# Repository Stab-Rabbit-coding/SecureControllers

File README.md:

# SecureControllers
unmanned system controllers with security baked in. 

These started as the avionics suite for the Serenity UAV, but aren't limited to that.

1. EMI-Hardened Beagle Capes

    * PocketBeagle2-I Secure Flight Controller
    * PocketBeagle2-I Secure Communications
    * PocketBeagle2-I Sub-Gigahertz Trustworthy Transceiver

2. Trustworthy Sensor R-PI HATs

2. Trustworthy Gateway devices

    * Stackable CAN+RS-485 peripherals Gateway for GPIO/SPI/TTL/ADC/DAC/UART with a TPM.

3. Trustworthy Final Control Elements

    * 50A ESC
    * digital servo
    * Camera/Laser pod
    * Power Distribution Board

## Engineering skills

`skills/` carries four draft Agent Skills for licensed-discipline engineering practice,
pulled from [Griffing-Technology-LLC/engineering-pe-skills](https://github.com/Griffing-Technology-LLC/engineering-pe-skills)
(MIT-licensed; see `skills/ATTRIBUTION.md` and `skills/LICENSE.upstream-MIT`):
`aeronautical-engineering`, `control-systems-engineering`, `mechanical-engineering`,
and `statics-and-dynamics`. **These are still works in progress and are not yet
reviewed or approved by a licensed Professional Engineer in the relevant discipline** —
see each skill's mandatory review notice before relying on any output.

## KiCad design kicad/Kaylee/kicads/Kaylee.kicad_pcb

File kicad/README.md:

# Serenity Avionics — KiCad Cape Status & Build Notes

This directory holds the KiCad projects for the four cape/board types:

| Project | Name | Role |
| --- | --- | --- |
| `Wash.kicad_*` | **Wash** | Flight-control & sensor cape (FC) |
| `TACCO.kicad_*` | **TACCO** | Comms / logging / payload cape (CN) |
| `FlightEngineer.kicad_*` | **FlightEngineer** | Power-distribution board (PDB) |
| `Emma.kicad_*` | **Emma** | 49 MHz (Part 15 §15.235) transceiver |
| `Observer.kicad_*` | **Observer** | Nose/Cargo vision, ToF, & laser board (standalone) |

Per-board net/pin documentation lives in the matching `*.md` files
(`Wash.md`, `TACCO.md`, `FlightEngineer.md`, `XCVR-49MHZ-2.md`). KiCad files keep
KiCad board coordinates (documented exception to the hull-frame standard,
see root `CLAUDE.md`).

---

## DRC / routing work — what was done and what was not (2026-06-12)

A pass was made to wire in a second Ethernet channel and to clear the
Design-Rule-Check (DRC) and ratsnest issues introduced by a manual
component rearrangement. This section records exactly what landed and
what is still open, so the thread can be picked up cleanly.

### ✅ Done

- **Second Ethernet (ETH2) wired on Wash.** The newly placed `ETH2`
  (JST-GH-4P), `ETH2-PHY` (ADIN1300BCPZ), and `T-ETH2` (749010012A
  magnetics) footprints were present but unconnected. Their nets now
  mirror the ETH1 topology exactly:

  ```text
  ETH2 ──ETH2_LINE_{TX,RX}{P,N}──► T-ETH2 ──ETH2_{TX,RX}{P,N}──► ETH2-PHY
  ```

  The host side reuses the nets already broken out on the **PB2-P2**
  header: the `RMII1_*` bus, shared `MDIO`/`MDC`, `PHY2_INTRN`/
  `PHY2_RSTN`, and the `VCC2_ETH` / `GND` / `GND2_ETH` power and
  isolation domains. 44 pads assigned (ETH2-PHY 32, T-ETH2 8, ETH2 4);
  diff-pair chains verified end-to-end. *(Delivered in PR #59.)*

- **Split the two Wash PHYs onto independent MDIO buses (2026-06-12).** Instead
  of an address strap on a shared bus, PHY1 now uses `MDIO0`/`MDC0` (the CPSW
  MDIO controller, PB2-P2 pins 17/18) and PHY2 uses `MDIO1`/`MDC1` (PB2-P2 pins
  1/2, the two spare servo channels SERVO6/7). Each PB2-I NIC manages its own
  PHY — no shared-address conflict. Both the PCB nets and the schematic global
  labels were updated. *Firmware note:* PHY2's bus is a second (bit-banged
  `mdio-gpio`) MDIO; confirm the two repurposed balls are GPIO-capable in the
  PB2-I pinmux.

- **Wired the floating field connectors to their signals (2026-06-12).** Every
  JST field connector was placed but had no nets. Using each footprint's
  Description pinout: SERVO-PWM pads 1–6 → `SERVO0–5` (servo PWM); ESC-TLM →
  `UART_ESC_TX`/`RX`; GPIO-A…F → `GND`/`+3V3` (+ labelled `GPIO_EXP_*` signal);
  CAN-FD → `CAN_H`/`CAN_L`; RS-485 → `RS485_A`/`B`; PWR-IN → `+5V`/`GND`. The
  new connector shorts that DRC now reports are all against `TMESH_*` (the
  pre-existing tamper-mesh overlap, resolved by the mesh rework below) — not the
  connector wiring itself.

- **Confirmed the design is PCB-driven.** Each cape's schematic
  (`*.kicad_sch`) defines only the PocketBeagle-2 header pin-mux (the
  PB2-P1/P2 connectors with the RMII0/RMII1/MDIO net labels); every other
  component lives as a PCB footprint with nets assigned directly on the
  board. "Update PCB from Schematic" therefore does **not** repopulate
  the component nets — net edits are made on the `.kicad_pcb`.

- **Verified the boards load** in `pcbnew` (Wash 43, TACCO 42, Emma 69,
  FlightEngineer 67 footprints) and characterised the violation landscape (below).

### ❌ Not done — open follow-up

1. **Tamper mesh (`TMESH_P`/`TMESH_N`).** Drawn today as a raw
   cross-hatch grid on F.Cu/B.Cu that **shorts across SMD pads and across
   the isolated `GND2_*` domains** — this is the single largest source of
   DRC errors (≈335 of Wash's 465; similar on TACCO). The agreed design is
   a **per-domain anti-tamper mesh**: a separate monitored mesh net per
   isolation region (secure/`GND` area plus one per `GND2_CAN` / `GND2_ETH`
   / `GND2_RS485` field side), with the 0.5 mm `ISOLATION` creepage moat
   kept clear between them. Wash and TACCO tie their mesh to the local TPM;
   **FlightEngineer and Emma have no local TPM**, so their tamper signal must be
   carried over the inter-board link (Emma → TACCO, FlightEngineer → Wash).

2. **Routing / ratsnest.** The manual rearrangement left signal nets
   unrouted (~60 multi-pin signal nets per cape; the 7 power/ground nets
   are intended as planes). This was **not** completed — see the toolchain
   findings below for why headless autorouting did not produce a
   trustworthy result. The impedance-controlled Ethernet pairs should be
   routed interactively (length-matched / controlled-impedance) regardless.

3. **Remaining DRC.** After the mesh and routing are fixed, the residual
   cosmetic/footprint items still need clearing (counts measured
   2026-06-12, error+warning):

   | Board | violations | unconnected | dominant types |
   | --- | --- | --- | --- |
   | Wash | 465 | 121 | mesh shorts, solder-mask bridges, clearance |
   | TACCO | 554 | 146 | mesh shorts, solder-mask bridges, clearance |
   | Emma | 421 | 160 | silk-over-copper, text-height, mask bridges |
   | FlightEngineer | 221 | 181 | courtyard overlap, lib-footprint mismatch, silk |

4. **MDIO addressing.** Both Wash PHYs (ETH1-PHY, ETH2-PHY) share the
   `MDIO`/`MDC` management bus but there are **no address-strap resistors
   on the board**, so both default to the same MDIO address. A strap
   (or a decision to manage each PHY only over its own RMII channel) is
   required before the second PHY is manageable. Not invented here because
   no strap-resistor footprints are placed.

---

## Toolchain findings (headless KiCad 9 + freerouting)

These are recorded so the next person does not re-derive them:

- **KiCad 9.0.2 `pcbnew.ExportSpecctraDSN()` is non-functional in
  standalone Python** — it returns `False` with no GUI/kiway context
  (`pcbnew.GetBoard()` is `None`). Loading a project, building
  connectivity, initialising a `wx.App`, and running under Xvfb all make
  no difference; it is a binding limitation, not a display issue.

- A custom headless **Specctra DSN exporter + SES importer** (driven
  entirely through the working board API) was written to bridge this. The
  round-trip is mechanically correct (valid DSN out, freerouting routes
  it, SES tracks/vias re-imported at the right coordinates).

- **freerouting 2.1.0 headless is unreliable for a complete route on this
  toolchain**: it must be run **without** a display (with Xvfb it opens
  the GUI and hangs); it never self-exits (must be killed after the SES is
  written); its multi-threaded optimiser is broken (use `-mt 1`); and the
  SES it emits captured only a handful of nets rather than the full
  ~60-net set. It was therefore **not** used to route the boards.

- **Recommended workflow:** finish routing in the **KiCad GUI** (where
  Specctra DSN export and the interactive/auto routers are reliable), with
  the Ethernet pairs routed by hand. The deterministic, non-routing work
  (per-domain tamper-mesh zones, cosmetic/footprint DRC, the Emma/FlightEngineer
  link tamper signalling) can still be scripted headless via the board API.

---

*Author: Steve Griffing, PE(CSE), CISSP-ISSEP, CPP · License: CC BY 4.0*

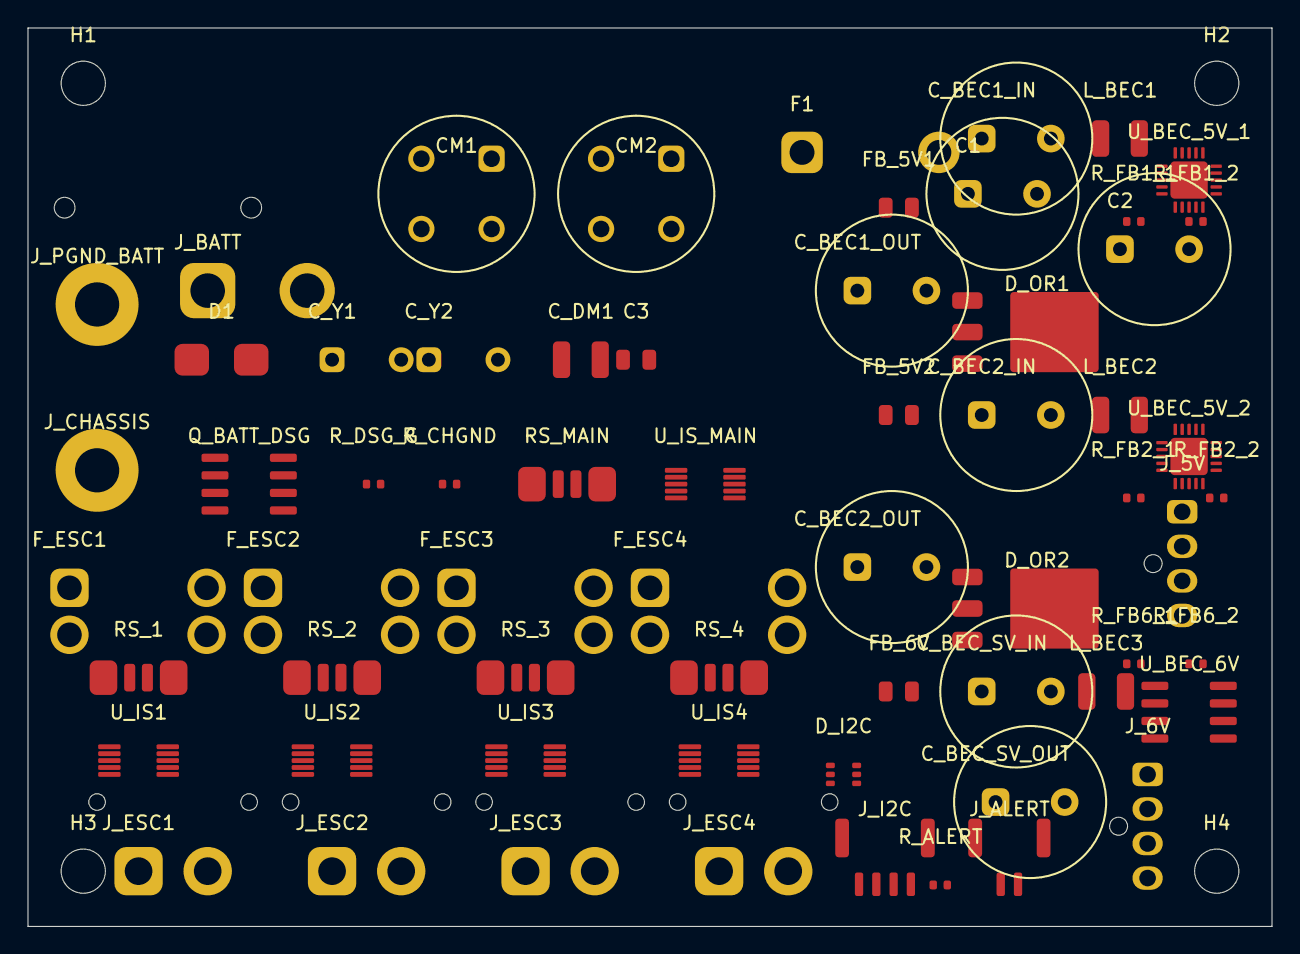
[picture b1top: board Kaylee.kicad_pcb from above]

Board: 4 copper layers, 90.0 x 65.0 mm, 67 parts (0 on the bottom side), 36 nets, no tracks yet.

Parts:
C1, C2: 220uF/35V; CP_Radial_D10.0mm_P5.00mm
C3: 100nF/50V; C_0805_2012Metric
CM1, CM2: WE-SL5_7440640500; CMC_WE-SL5_7440640500
C_BEC1_IN, C_BEC1_OUT, C_BEC2_IN, C_BEC2_OUT: 100uF/50V; CP_Radial_D10.0mm_P5.00mm
C_BEC_SV_IN: 100uF/50V; CP_Radial_D10.0mm_P5.00mm
C_BEC_SV_OUT: 100uF/50V; CP_Radial_D10.0mm_P5.00mm
C_DM1: 10uF/50V; L_1210_3225Metric
C_Y1, C_Y2: 4.7nF/250V_Y2; C_Disc_D4.3mm_W1.9mm_P5.00mm
D1: SMBJ33CA; D_SMB
D_I2C: PRTR5V0U2X; SOT-363_SC-70-6
D_OR1, D_OR2: MBRD1045CT; TO-252-3_TabPin2
F1: FuseHolder_MAXI_150A; FuseHolder_MAXI_PCB
FB_5V1, FB_5V2, FB_6V: WE-742792612; C_0805_2012Metric
F_ESC1, F_ESC2, F_ESC3, F_ESC4: FuseHolder_Mini_40A; Fuseholder_Blade_Mini_Keystone_3568
H1, H2, H3, H4: M3; MountingHole_3.2mm_M3
J_5V: NanoFit-4P_5V; Molex_Nano-Fit_105309-xx04_1x04_P2.50mm_Vertical
J_6V: NanoFit-4P_6V; Molex_Nano-Fit_105309-xx04_1x04_P2.50mm_Vertical
J_ALERT: JST-GH_2P_ALERT; JST_GH_BM02B-GHS-TBT_1x02-1MP_P1.25mm_Vertical
J_BATT: XT60PW-F; AMASS_XT60PW-F_1x02_P7.20mm_Horizontal
J_CHASSIS: M3_Lug; MountingHole_3.2mm_M3_Pad_Via
J_ESC1: XT30PW-F_ESC1; AMASS_XT30PW-F_1x02_P2.50mm_Horizontal
J_ESC2: XT30PW-F_ESC2; AMASS_XT30PW-F_1x02_P2.50mm_Horizontal
J_ESC3: XT30PW-F_ESC3; AMASS_XT30PW-F_1x02_P2.50mm_Horizontal
J_ESC4: XT30PW-F_ESC4; AMASS_XT30PW-F_1x02_P2.50mm_Horizontal
J_I2C: JST-GH_4P_I2C; JST_GH_BM04B-GHS-TBT_1x04-1MP_P1.25mm_Vertical
J_PGND_BATT: M3_Lug; MountingHole_3.2mm_M3_Pad_Via
L_BEC1, L_BEC2, L_BEC3: WE-744314100_10uH; L_1210_3225Metric
Q_BATT_DSG: AON6556; SOIC-8_3.9x4.9mm_P1.27mm
RS_1, RS_2, RS_3, RS_4: 1mOhm_Kelvin_2512; R_Shunt_CSS2H_2512K
RS_MAIN: 1mOhm_Kelvin_2512; R_Shunt_CSS2H_2512K
R_ALERT: 2.2k; R_0402_1005Metric
R_CHGND: 0R; R_0402_1005Metric
R_DSG_G: 10k; R_0402_1005Metric
R_FB1_1, R_FB2_1, R_FB6_1: 100k; R_0402_1005Metric
R_FB1_2, R_FB2_2: 22.1k; R_0402_1005Metric
R_FB6_2: 30.1k; R_0402_1005Metric
U_BEC_5V_1, U_BEC_5V_2: TPS54620RGYT; Texas_RGP0020D_VQFN-20-1EP_4x4mm_P0.5mm_EP2.7x2.7mm
U_BEC_6V: TPS54540DDAR; SOIC-8_3.9x4.9mm_P1.27mm
U_IS1: INA226_0x40; MSOP-10_3x3mm_P0.5mm
U_IS2: INA226_0x41; MSOP-10_3x3mm_P0.5mm
U_IS3: INA226_0x42; MSOP-10_3x3mm_P0.5mm
U_IS4: INA226_0x43; MSOP-10_3x3mm_P0.5mm
U_IS_MAIN: INA226_0x44; MSOP-10_3x3mm_P0.5mm

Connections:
+5V: D_I2C.6, D_OR1.2, D_OR2.2, J_5V.3, J_5V.4, J_I2C.2, R_ALERT.1, U_IS1.4, U_IS2.4, U_IS3.4, U_IS4.4, U_IS_MAIN.4
+6V: C_BEC_SV_OUT.1, J_6V.3, J_6V.4, R_FB6_1.1, U_BEC_6V.6
BEC1_PRE_OR: C_BEC1_OUT.1, D_OR1.1, R_FB1_1.1, U_BEC_5V_1.11
BEC1_SW: L_BEC1.2, U_BEC_5V_1.5, U_BEC_5V_1.6
BEC1_VIN_F: C_BEC1_IN.1, FB_5V1.2, L_BEC1.1, U_BEC_5V_1.1, U_BEC_5V_1.15, U_BEC_5V_1.16, U_BEC_5V_1.17, U_BEC_5V_1.18, U_BEC_5V_1.19, U_BEC_5V_1.20
BEC2_PRE_OR: C_BEC2_OUT.1, D_OR1.3, D_OR2.1, D_OR2.3, R_FB2_1.1, U_BEC_5V_2.11
BEC2_SW: L_BEC2.2, U_BEC_5V_2.5, U_BEC_5V_2.6
BEC2_VIN_F: C_BEC2_IN.1, FB_5V2.2, L_BEC2.1, U_BEC_5V_2.1, U_BEC_5V_2.15, U_BEC_5V_2.16, U_BEC_5V_2.17, U_BEC_5V_2.18, U_BEC_5V_2.19, U_BEC_5V_2.20
BEC6V_SW: L_BEC3.2, U_BEC_6V.8
BEC6V_VIN_F: C_BEC_SV_IN.1, FB_6V.2, L_BEC3.1, U_BEC_6V.2, U_BEC_6V.3, U_BEC_6V.4
CHASSIS: C_Y1.2, C_Y2.2, R_CHGND.2
DSG_GATE: Q_BATT_DSG.8, R_DSG_G.1
ESC1_FUSED: F_ESC1.2, RS_1.1, U_IS1.10
ESC1_RS_OUT: J_ESC1.1, RS_1.4
ESC1_SNS_N: RS_1.3, U_IS1.2
ESC1_SNS_P: RS_1.2, U_IS1.1
ESC2_FUSED: F_ESC2.2, RS_2.1, U_IS2.10
ESC2_RS_OUT: J_ESC2.1, RS_2.4
ESC2_SNS_N: RS_2.3, U_IS2.2
ESC2_SNS_P: RS_2.2, U_IS2.1
ESC3_FUSED: F_ESC3.2, RS_3.1, U_IS3.10
ESC3_RS_OUT: J_ESC3.1, RS_3.4
ESC3_SNS_N: RS_3.3, U_IS3.2
ESC3_SNS_P: RS_3.2, U_IS3.1
ESC4_FUSED: F_ESC4.2, RS_4.1, U_IS4.10
ESC4_RS_OUT: J_ESC4.1, RS_4.4
ESC4_SNS_N: RS_4.3, U_IS4.2
ESC4_SNS_P: RS_4.2, U_IS4.1
MAIN_SNS_N: RS_MAIN.3, U_IS_MAIN.2
MAIN_SNS_P: RS_MAIN.2, U_IS_MAIN.1
PDB_ALERT_N: J_ALERT.2, R_ALERT.2, U_IS1.7, U_IS2.7, U_IS3.7, U_IS4.7, U_IS_MAIN.7
PDB_SCL: D_I2C.4, J_I2C.3, U_IS1.6, U_IS2.6, U_IS3.6, U_IS4.6, U_IS_MAIN.6
PDB_SDA: D_I2C.5, J_I2C.4, U_IS1.5, U_IS2.5, U_IS3.5, U_IS4.5, U_IS_MAIN.5
PGND: C1.2, C2.2, C3.2, CM1.3, CM1.4, CM2.3, CM2.4, C_BEC1_IN.2, C_BEC1_OUT.2, C_BEC2_IN.2, C_BEC2_OUT.2, C_BEC_SV_IN.2, C_BEC_SV_OUT.2, C_DM1.2, C_Y2.1, D1.1, D_I2C.1, J_5V.1, J_5V.2, J_6V.1, J_6V.2, J_ALERT.1, J_BATT.2, J_ESC1.2, J_ESC2.2, J_ESC3.2, J_ESC4.2, J_I2C.1, R_CHGND.1, R_DSG_G.2, R_FB1_2.2, R_FB2_2.2, R_FB6_2.2, U_BEC_5V_1.7, U_BEC_5V_1.8, U_BEC_5V_1.9, U_BEC_5V_1.10, U_BEC_5V_1.21, U_BEC_5V_2.7, U_BEC_5V_2.8, U_BEC_5V_2.9, U_BEC_5V_2.10, U_BEC_5V_2.21, U_IS1.3, U_IS2.3, U_IS3.3, U_IS4.3, U_IS_MAIN.3
VBAT: F_ESC1.1, F_ESC2.1, F_ESC3.1, F_ESC4.1, Q_BATT_DSG.1, Q_BATT_DSG.2, Q_BATT_DSG.3, Q_BATT_DSG.4, RS_MAIN.1, RS_MAIN.4, U_IS_MAIN.10
VDIS: C1.1, C2.1, C3.1, CM1.1, CM1.2, CM2.1, CM2.2, C_DM1.1, C_Y1.1, D1.2, F1.1, F1.2, FB_5V1.1, FB_5V2.1, FB_6V.1, J_BATT.1, Q_BATT_DSG.5, Q_BATT_DSG.6, Q_BATT_DSG.7

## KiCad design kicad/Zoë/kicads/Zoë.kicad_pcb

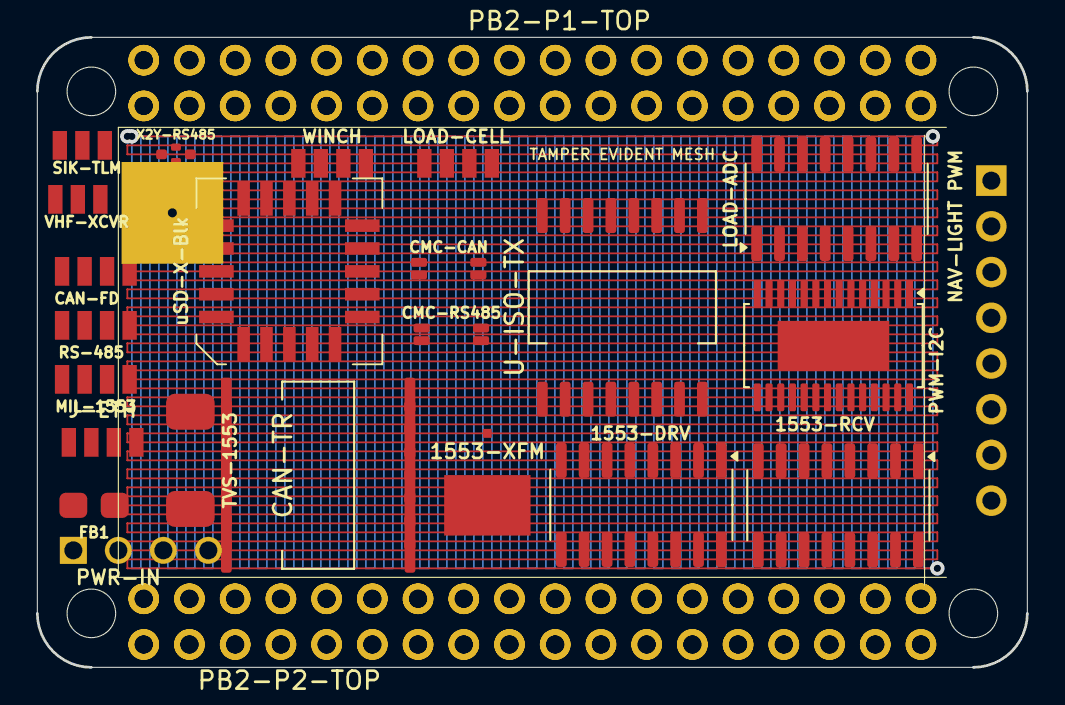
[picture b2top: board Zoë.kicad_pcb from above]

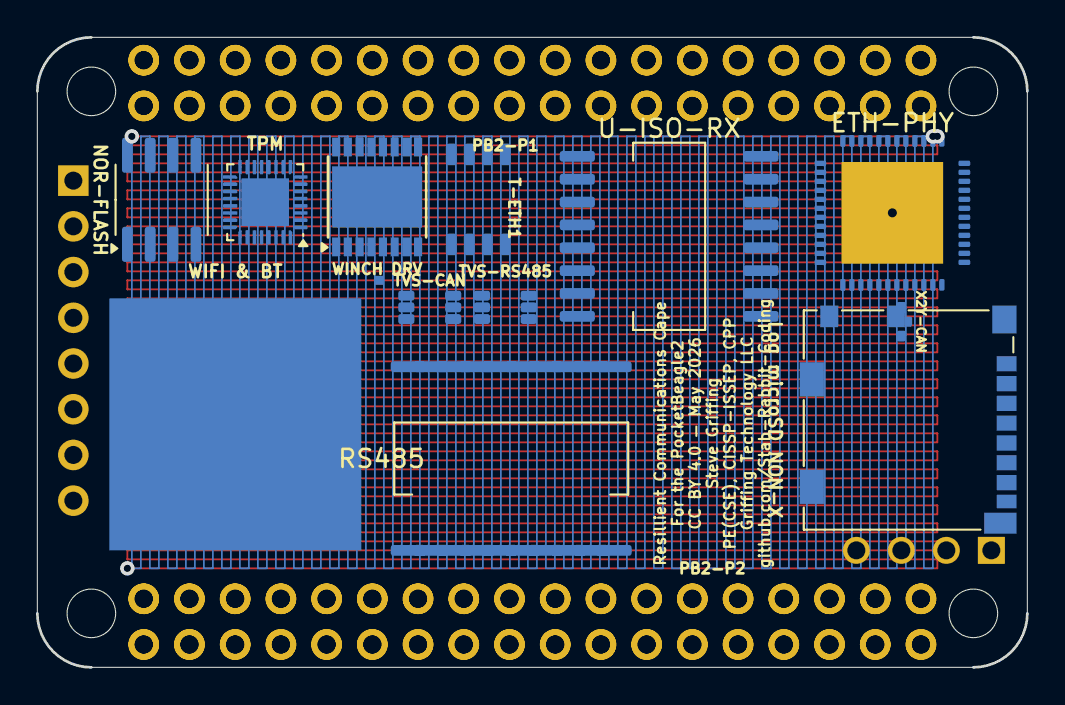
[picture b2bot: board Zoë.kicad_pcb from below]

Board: 4 copper layers, 55.0 x 35.0 mm, 39 parts (14 on the bottom side), 85 nets.

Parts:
1553-DRV: DS26LV31; SOIC-16_3.9x9.9mm_P1.27mm
1553-RCV: DS26LV32; SOIC-16_3.9x9.9mm_P1.27mm
1553-XFM: SM-1553-11; Package
CAN-FD: JST-GH-4P-CAN; JST_GH_4P
CAN-TR: ISOW1044BDFMR; SOIC-16W_7.5x10.3mm_P1.27mm
CMC-CAN: SRF2012-100Y; Bourns_SRF2012_4T
CMC-RS485: SRF2012-100Y; Bourns_SRF2012_4T
ETH-PHY: ADIN1300BCPZ; QFN-48-1EP_7x7mm_P0.5mm_EP5.65x5.65mm
FB1: 742792512; C_0805_2012Metric
J-ETH: JST-GH-4P-ETH; JST_GH_4P
LOAD-ADC: HX711; SOIC-16_3.9x9.9mm_P1.27mm
LOAD-CELL: JST-GH-4P-LOAD-CELL; JST_GH_4P
Log microSD NON-X: microSD-Log; microSD_HC_Molex_104031-0811
MIL-1553: JST-GH-4P-1553; JST_GH_4P
NAV-LIGHT PWM: 1x8-NavLight-PWM; Connector_PinHeader_2.54mm
NOR-FLASH: W25Q128JV; SOIC-8_3.9x4.9mm_P1.27mm
PB2-P1, PB2-P1-TOP: PB2I-P1-2x18; 2x18_P1_Socket
PB2-P2, PB2-P2-TOP: PB2I-P2-2x18; 2x18_P2_Socket
PWM-I2C: PCA9685; HTSSOP-28-1EP_4.4x9.7mm_P0.65mm_EP2.75x6.2mm
PWR-IN: Nano-Fit-4P-POWER; Connector_Molex_NanoFit
RS485: ADM2795EBRWZ; SOIC-20W_7.5x12.8mm_P1.27mm
RS-485: JST-GH-4P-RS485; JST_GH_4P
SIK-TLM: JST-GH-3P-SiK; JST_GH_3P
T-ETH1: 749010012A; ETH_XFMR_8P_5x3.5mm
TPM: SLB9670; QFN-32-1EP_4x4mm_P0.4mm_EP2.65x2.65mm
TVS-1553: SMAJ33CA; DO-214AC_SMA
TVS-CAN: PRTR5V0U2X; SOT-363_SC-88
TVS-RS485: PRTR5V0U2X; SOT-363_SC-88
U-ISO-RX: ISO7642FDWRR; SOIC-16W_7.5x10.3mm_P1.27mm
U-ISO-TX: ISO7642FDWRR; SOIC-16W_7.5x10.3mm_P1.27mm
VHF-XCVR: JST-GH-3P-RCRS; JST_GH_3P
WIFI & BT: WL1837MOD; RF_Module
WINCH: JST-GH-4P-WINCH; JST_GH_4P
WINCH DRV: DRV8833; HTSSOP-16-1EP_4.4x5mm_P0.65mm_EP3.4x5mm
X2Y-CAN, X2Y-RS485: 4.7nF X2Y; X2Y_Cap_4T_0402
uSD-X-Blk: ATF16V8BQL; PLCC-20

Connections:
+3V3: CAN-TR.1, PB2-P1.33, PB2-P1.34, PB2-P1-TOP.33, PB2-P1-TOP.34, RS485.1, U-ISO-RX.16, U-ISO-TX.1
+5V: FB1.1, FB1.2, PB2-P1.35, PB2-P1-TOP.35, PB2-P2.35, PB2-P2-TOP.35
CAN_H: CAN-TR.9, CMC-CAN.1, CMC-CAN.3, TVS-CAN.1
CAN_L: CAN-TR.10, CMC-CAN.2, CMC-CAN.4, TVS-CAN.3
CAN_STB: CAN-TR.3, PB2-P1.12, PB2-P1-TOP.12
ETH_LINE_RXN: J-ETH.4, T-ETH1.8
ETH_LINE_RXP: J-ETH.3, T-ETH1.7
ETH_LINE_TXN: J-ETH.2, T-ETH1.6
ETH_LINE_TXP: J-ETH.1, T-ETH1.5
ETH_RXN: ETH-PHY.5, T-ETH1.4
ETH_RXP: ETH-PHY.4, T-ETH1.3
ETH_TXN: ETH-PHY.2, T-ETH1.2
ETH_TXP: ETH-PHY.1, T-ETH1.1
GND: CAN-TR.8, ETH-PHY.3, ETH-PHY.6, ETH-PHY.10, ETH-PHY.11, ETH-PHY.12, ETH-PHY.49, PB2-P1.1, PB2-P1.2, PB2-P1.36, PB2-P1-TOP.1, PB2-P1-TOP.2, PB2-P1-TOP.36, PB2-P2.36, PB2-P2-TOP.36, RS485.2, RS485.7, RS485.8, TVS-1553.1, U-ISO-RX.9, U-ISO-TX.8, X2Y-CAN.1, X2Y-CAN.2, X2Y-CAN.3, X2Y-RS485.1, X2Y-RS485.2, X2Y-RS485.3
GND2_CAN: CAN-TR.12, CAN-TR.13, TVS-CAN.2, X2Y-CAN.4
GND2_ETH: ETH-PHY.21, ETH-PHY.22, ETH-PHY.25, ETH-PHY.34, ETH-PHY.36, U-ISO-RX.8, U-ISO-TX.9
GND2_RS485: RS485.12, RS485.13, RS485.18, RS485.19, TVS-RS485.2, X2Y-RS485.4
I2C0_SCL: PB2-P1.4, PB2-P1-TOP.4, PWM-I2C.24
I2C0_SDA: PB2-P1.3, PB2-P1-TOP.3, PWM-I2C.22
LOAD_CELL_DOUT: PB2-P2.7, PB2-P2-TOP.7
LOAD_CELL_SCK: LOAD-ADC.16, PB2-P2.8, PB2-P2-TOP.8
LORA_DIO0: PB2-P1.20, PB2-P1-TOP.20
LORA_RESETN: PB2-P1.19, PB2-P1-TOP.19
MCAN1_RX: CAN-TR.4, PB2-P1.13, PB2-P1-TOP.13
MCAN1_TX: CAN-TR.2, PB2-P1.14, PB2-P1-TOP.14
MDC: ETH-PHY.19, PB2-P2.18, PB2-P2-TOP.18, U-ISO-TX.6, U-ISO-TX.11
MDIO: ETH-PHY.18, PB2-P2.17, PB2-P2-TOP.17, U-ISO-RX.7, U-ISO-RX.10
PHY1_INTRN: ETH-PHY.20, PB2-P2.16, PB2-P2-TOP.16, U-ISO-RX.6, U-ISO-RX.11
PHY1_RSTN: ETH-PHY.35, PB2-P2.15, PB2-P2-TOP.15, U-ISO-TX.7, U-ISO-TX.10
PHY2_INTRN: PB2-P2.14, PB2-P2-TOP.14
PHY2_RSTN: PB2-P2.13, PB2-P2-TOP.13
PRU_1553_RX_N: 1553-RCV.13, PB2-P1.5, PB2-P1-TOP.5
PRU_1553_RX_P: PB2-P1.6, PB2-P1-TOP.6
PRU_1553_TX_N: 1553-DRV.6, PB2-P1.7, PB2-P1-TOP.7
PRU_1553_TX_P: 1553-DRV.10, PB2-P1.8, PB2-P1-TOP.8
PWM_CH0: PB2-P2.6, PB2-P2-TOP.6, uSD-X-Blk.6
PWM_CH1: PB2-P2.5, PB2-P2-TOP.5, PWM-I2C.11, uSD-X-Blk.5
PWM_CH2: PB2-P2.4, PB2-P2-TOP.4, PWM-I2C.10, uSD-X-Blk.4
PWM_CH3: PB2-P2.3, PB2-P2-TOP.3, PWM-I2C.9, uSD-X-Blk.3
RMII0_CRS_DV: ETH-PHY.32, PB2-P2.29, PB2-P2-TOP.29, U-ISO-RX.4, U-ISO-RX.13
RMII0_REF_CLK: ETH-PHY.29, PB2-P2.27, PB2-P2-TOP.27, U-ISO-TX.2, U-ISO-TX.15
RMII0_RXD0: ETH-PHY.30, PB2-P2.31, PB2-P2-TOP.31, U-ISO-RX.2, U-ISO-RX.15
RMII0_RXD1: ETH-PHY.31, PB2-P2.30, PB2-P2-TOP.30, U-ISO-RX.3, U-ISO-RX.14
RMII0_RX_ER: ETH-PHY.33, PB2-P2.28, PB2-P2-TOP.28, U-ISO-RX.5, U-ISO-RX.12
RMII0_TXD0: ETH-PHY.28, PB2-P2.34, PB2-P2-TOP.34, U-ISO-TX.3, U-ISO-TX.14
RMII0_TXD1: ETH-PHY.27, PB2-P2.33, PB2-P2-TOP.33, U-ISO-TX.4, U-ISO-TX.13
RMII0_TX_EN: ETH-PHY.26, PB2-P2.32, PB2-P2-TOP.32, U-ISO-TX.5, U-ISO-TX.12
RMII1_CRS_DV: PB2-P2.21, PB2-P2-TOP.21
RMII1_REF_CLK: PB2-P2.19, PB2-P2-TOP.19
RMII1_RXD0: PB2-P2.23, PB2-P2-TOP.23
RMII1_RXD1: PB2-P2.22, PB2-P2-TOP.22
RMII1_RX_ER: PB2-P2.20, PB2-P2-TOP.20
RMII1_TXD0: PB2-P2.26, PB2-P2-TOP.26
RMII1_TXD1: PB2-P2.25, PB2-P2-TOP.25
RMII1_TX_EN: PB2-P2.24, PB2-P2-TOP.24
RS485_A: CMC-RS485.1, CMC-RS485.3, RS485.14, TVS-RS485.1
RS485_B: CMC-RS485.2, CMC-RS485.4, RS485.15, TVS-RS485.3
RS485_DE: PB2-P1.9, PB2-P1-TOP.9, RS485.4, RS485.5
RS485_RX: PB2-P1.10, PB2-P1-TOP.10, RS485.6
RS485_TX: PB2-P1.11, PB2-P1-TOP.11, RS485.3
SDIO_CLK: Log microSD NON-X.6, PB2-P1.32, PB2-P1-TOP.32
SDIO_CMD: Log microSD NON-X.8, PB2-P1.31, PB2-P1-TOP.31
SDIO_D0: Log microSD NON-X.4, PB2-P1.30, PB2-P1-TOP.30
SDIO_D1: PB2-P1.29, PB2-P1-TOP.29
SDIO_D2: Log microSD NON-X.3, PB2-P1.28, PB2-P1-TOP.28
SDIO_D3: PB2-P1.27, PB2-P1-TOP.27
SERVO6: PB2-P2.2, PB2-P2-TOP.2
SERVO7: PB2-P2.1, PB2-P2-TOP.1, uSD-X-Blk.15
SPI1_CLK: NOR-FLASH.2, PB2-P1.25, PB2-P1-TOP.25, TPM.23
SPI1_CS_LORA: PB2-P1.26, PB2-P1-TOP.26
SPI1_CS_NOR: NOR-FLASH.3, PB2-P1.22, PB2-P1-TOP.22
SPI1_CS_TPM: PB2-P1.21, PB2-P1-TOP.21, TPM.28
SPI1_MISO: NOR-FLASH.6, PB2-P1.23, PB2-P1-TOP.23, TPM.22
SPI1_MOSI: NOR-FLASH.5, PB2-P1.24, PB2-P1-TOP.24, TPM.21
TPM_IRQN: PB2-P2.12, PB2-P2-TOP.12, TPM.24
TPM_RSTN: PB2-P2.11, PB2-P2-TOP.11, TPM.1
UART_RCRS_RX: PB2-P1.15, PB2-P1-TOP.15
UART_RCRS_TX: PB2-P1.16, PB2-P1-TOP.16
UART_SIK_RX: PB2-P1.17, PB2-P1-TOP.17
UART_SIK_TX: PB2-P1.18, PB2-P1-TOP.18
VCC2_CAN: CAN-TR.14, TVS-CAN.5
VCC2_ETH: ETH-PHY.7, ETH-PHY.8, ETH-PHY.9, ETH-PHY.40, ETH-PHY.41, U-ISO-RX.1, U-ISO-TX.16
VCC2_RS485: RS485.11, RS485.20, TVS-RS485.5
WINCH_IN1: PB2-P2.10, PB2-P2-TOP.10, WINCH DRV.5
WINCH_IN2: PB2-P2.9, PB2-P2-TOP.9, WINCH DRV.8

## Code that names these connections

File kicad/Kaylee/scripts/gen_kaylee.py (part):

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

def lib_symbol_m3pad(name="M3_ChassisPad"):
    """Single-pin M3 chassis ground lug pad."""
    return f"""  (symbol "{name}" (in_bom yes) (on_board yes)
    (property "Reference" "TP" (at 0 -2.54 0) (effects (font (size 1.27 1.27))))
    (property "Value" "{name}" (at 0 2.54 0) (effects (font (size 1.27 1.27))))
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      (circle (center 0 0) (radius 1.0)
        (stroke (width 0.254) (type default)) (fill (type background))))
    (symbol "{name}_1_1"
{_pin_def("passive","line",-2.54,0,0,1.54,"PGND","1")})
  )"""


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    # -----------------------------------------------------------------------
    parts.append(text_note("=== Section A: Battery Input / Main Bus Filter ===", 10, 15))

    # J_BATT (XT60PW-F) — battery connector, pin1=+VBAT, pin2=PGND
    cx, cy = 20, 30
    parts.append(sym_inst("XT60PW_F", "J_BATT", "Amass XT60PW-F", cx, cy))
    parts.append(glabel("VBAT_IN_P", cx + 2.54, cy - 1.27, rot=0))
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    # C_Y1, C_Y2 — Y-class CM bypass caps
    parts.append(sym_inst("C_Generic", "C_Y1", "Kemet SA305E472MAR 4.7nF/250V Y2", 58, 48))
    parts.append(pwr_sym("VBAT",  58 - 2.54, 48, rot=0))
    parts.append(glabel("CHASSIS", 58 + 2.54, 48, rot=0))

    parts.append(sym_inst("C_Generic", "C_Y2", "Kemet SA305E472MAR 4.7nF/250V Y2", 65, 48))
    parts.append(pwr_sym("PGND",  65 - 2.54, 48, rot=0))
    parts.append(glabel("CHASSIS", 65 + 2.54, 48, rot=0))

    # -----------------------------------------------------------------------
    # Section B: Disconnect FET + main shunt + main INA226  (x=105..200, y=30)
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    # Q_BATT_DSG (AON6556): G=DSG_GATE, S=PGND, D=VBAT→VDIS
    cx, cy = 120, 30
    parts.append(sym_inst("AON6556", "Q_BATT_DSG", "AON6556 60V/30A NMOS", cx, cy))
    parts.append(glabel("DSG_GATE", cx - 7.62, cy - 2.54, rot=180))
    parts.append(pwr_sym("PGND",    cx - 7.62, cy + 2.54, rot=0))
    parts.append(pwr_sym("VBAT",    cx + 7.62, cy,         rot=180))

    # R_DSG_G — gate resistor 10k
    parts.append(sym_inst("R_Generic", "R_DSG_G", "10k 0402", cx - 12, cy + 10))
    parts.append(glabel("BQ_DSG_OUT", cx - 12 - 2.54, cy + 10, rot=180))
    parts.append(glabel("DSG_GATE",   cx - 12 + 2.54, cy + 10, rot=0))

    # R_CHGND — 0 Ohm chassis-PGND bond (socketed)
    parts.append(sym_inst("R_Generic", "R_CHGND", "0R 0402 (chassis-PGND bond, configurable)", cx - 12, cy + 18))
    parts.append(glabel("CHASSIS",    cx - 12 - 2.54, cy + 18, rot=180))
    parts.append(pwr_sym("PGND",      cx - 12 + 2.54, cy + 18, rot=180))

    # J_CHASSIS — M3 standoff pads (chassis bond point)
    parts.append(sym_inst("M3_ChassisPad", "J_CHASSIS", "M3 x8 brass standoff (x4)", cx - 5, cy + 25))
    parts.append(glabel("CHASSIS",    cx - 5 - 2.54, cy + 25, rot=180))

    # RS_MAIN — 1mΩ 4-terminal shunt (after Q_BATT_DSG drain, before VDIS)
    cx, cy = 150, 30
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    parts.append(pwr_sym("+5V",        cx - 10.16, cy + 2.54,  rot=0))   # VS
    # A0=GND (0x44: A0=GND, A1=VCC)
    parts.append(pwr_sym("PGND",       cx - 10.16, cy + 5.08,  rot=0))   # A0=GND
    parts.append(glabel("PDB_SDA",     cx + 10.16, cy - 5.08,  rot=0))   # SDA
    parts.append(glabel("PDB_SCL",     cx + 10.16, cy - 2.54,  rot=0))   # SCL
    parts.append(glabel("PDB_ALERT_N", cx + 10.16, cy,          rot=0))  # ALERT
    parts.append(pwr_sym("+5V",        cx + 10.16, cy + 2.54,  rot=180)) # A1=VCC (addr bit)
    parts.append(glabel("VDIS_SENSE",  cx + 10.16, cy + 5.08,  rot=0))  # VBUS

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            parts.append(pwr_sym(a0_net,       cx2 - 10.16, cy2 + 5.08,  rot=0))
        else:
            parts.append(glabel(a0_net,        cx2 - 10.16, cy2 + 5.08, rot=180))
        parts.append(glabel("PDB_SDA",         cx2 + 10.16, cy2 - 5.08, rot=0))
        parts.append(glabel("PDB_SCL",         cx2 + 10.16, cy2 - 2.54, rot=0))
        parts.append(glabel("PDB_ALERT_N",     cx2 + 10.16, cy2,         rot=0))
        # A1 pin
        if a1_net in ("PGND", "+5V"):
            parts.append(pwr_sym(a1_net,       cx2 + 10.16, cy2 + 2.54, rot=180))
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    # BAT+ (pack reference)
    parts.append(pwr_sym("VBAT",      ucx + 15.24, ucy - 15.24,  rot=180))
    # SDA/SCL
    parts.append(glabel("PDB_SDA",    ucx + 15.24, ucy - 12.70,  rot=0))
    parts.append(glabel("PDB_SCL",    ucx + 15.24, ucy - 10.16,  rot=0))
    # ALERT_N
    parts.append(glabel("PDB_ALERT_N", ucx + 15.24, ucy - 7.62,  rot=0))
    # DSG gate
    parts.append(glabel("BQ_DSG_OUT", ucx + 15.24, ucy - 5.08,   rot=0))
    # CHG gate — no-connect (DNP charge FET path)
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    parts.append(glabel("PDB_SCL_RAW", 555 - 7.62, 35 + 2.54, rot=180))
    parts.append(pwr_sym("+5V",        555 + 7.62, 35 - 2.54, rot=180))
    parts.append(nc(555 + 7.62, 35))                             # D2A — unused second diode anode
    parts.append(glabel("PDB_SDA",     555 + 7.62, 35 + 2.54, rot=0))

    # Short wire: PDB_SDA_RAW == PDB_SDA at this device boundary
    # (The TVS routes PDB_SDA through D_I2C; both labels used at ports)
    # Tie SCL through similarly
    parts.append(glabel("PDB_SCL_RAW", 548, 45, rot=180))
    parts.append(glabel("PDB_SCL",     552, 45, rot=0))

    # R_ALERT — 2.2kΩ pull-up for ALERT_N bus
    parts.append(sym_inst("R_Generic", "R_ALERT", "2.2k 0402 ALERT pull-up to +5V", 570, 50))
    parts.append(pwr_sym("+5V",         570 - 2.54, 50, rot=0))
    parts.append(glabel("PDB_ALERT_N",  570 + 2.54, 50, rot=0))

    # J_I2C — JST-GH 4-pin to Wash/Shepherd Bay A
    parts.append(sym_inst("Conn_JST_GH_04P", "J_I2C",
                          "JST-GH SM04B-GHS-TB 4P 1.25mm PDB I2C to FC1", 590, 38))
    parts.append(pwr_sym("PGND",        590 + 2.54, 38 - 3.81, rot=180))
    parts.append(pwr_sym("+5V",         590 + 2.54, 38 - 1.27, rot=0))
    parts.append(glabel("PDB_SCL",      590 + 2.54, 38 + 1.27, rot=0))
    parts.append(glabel("PDB_SDA",      590 + 2.54, 38 + 3.81, rot=0))

    parts.append(sym_inst("M3_ChassisPad", "J_SHLD_I2C", "PGND via-pad I2C cable shield", 590, 52))
    parts.append(pwr_sym("PGND", 590 - 2.54, 52, rot=0))
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    parts.append(sym_inst("Conn_JST_GH_02P", "J_ALERT",
                          "JST-GH SM02B-GHS-TB 2P 1.25mm ALERT to Wash GPIO", 590, 65))
    parts.append(pwr_sym("PGND",        590 + 2.54, 65 - 1.27, rot=180))
    parts.append(glabel("PDB_ALERT_N",  590 + 2.54, 65 + 1.27, rot=0))

    parts.append(sym_inst("M3_ChassisPad", "J_SHLD_ALERT", "PGND via-pad ALERT cable shield", 590, 75))
    parts.append(pwr_sym("PGND", 590 - 2.54, 75, rot=0))
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
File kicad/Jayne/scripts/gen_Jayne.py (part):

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        )
    )
    parts.append(glabel("GND", 20 - 3.81, 55, rot=180))
    parts.append(glabel("PGND", 20 + 3.81, 55, rot=0))
    parts.append(
        sym_inst(
            "C_Generic",
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        )
    )
    parts.append(glabel("GND", 20 - 3.81, 60, rot=180))
    parts.append(glabel("PGND", 20 + 3.81, 60, rot=0))

    cx, cy = 55, 40
    parts.append(sym_inst("TI_TPS65219", "U_PMIC", "TPS65219 PMIC", cx, cy))
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    parts.append(
        glabel_pin("RGMII1_RXD0", cx, cy, AM62A_L, AM62A_R, "RGMII1_RXD0", AM62A_SIZE)
    )
    parts.append(glabel_pin("MDIO", cx, cy, AM62A_L, AM62A_R, "MDIO", AM62A_SIZE))
    parts.append(glabel_pin("MDC", cx, cy, AM62A_L, AM62A_R, "MDC", AM62A_SIZE))
    # UART link to U3 (MSPM0G3507): crossed TX->RX, not net-name-matched TX->TX.
    parts.append(
        glabel_pin("UART_A2M", cx, cy, AM62A_L, AM62A_R, "MCU_UART_TX", AM62A_SIZE)
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        glabel_pin("SW_SPI_SCK", cx, cy, MSPM0_L, MSPM0_R, "SPI1_SCK", MSPM0_SIZE)
    )
    parts.append(
        glabel_pin("SW_SPI_MOSI", cx, cy, MSPM0_L, MSPM0_R, "SPI1_MOSI", MSPM0_SIZE)
    )
    parts.append(
        glabel_pin("SW_SPI_MISO", cx, cy, MSPM0_L, MSPM0_R, "SPI1_MISO", MSPM0_SIZE)
    )
    parts.append(
        glabel_pin("LASER_EN", cx, cy, MSPM0_L, MSPM0_R, "GPIO_LASER_EN", MSPM0_SIZE)
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        "J_ETH_OUT",
    )

    parts.append(glabel("PGND", 300, 240, rot=0))
    parts.append(glabel("PGND_SHIELD", 300, 243, rot=0))

    # =====================================================================
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    )
    parts.append(glabel_pin("CANFD_H", cx2, cy2, TVS_L, TVS_R, "A1", TVS_SIZE))
    parts.append(glabel_pin("CANFD_L", cx2, cy2, TVS_L, TVS_R, "A2", TVS_SIZE))
    parts.append(pwr_pin("PGND", cx2, cy2, TVS_L, TVS_R, "K", TVS_SIZE))

    # J_CANFD connector
    cx, cy = 100, 235
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
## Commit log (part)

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2026-06-02 reorganized
2026-06-02 fixed and reorged
2026-06-02 Add EMI-hardened KiCad project files for CAPE-A-2, CAPE-B-2, and XCVR-49MHZ-2
    Project files (.kicad_pro, .kicad_prl) and design notes (.md) for three
    EMI-hardened board variants targeting IEC 61000-4-2/4/5 Level 3-4 and
    MIL-STD-461G RS103 200 V/m.
    Key design choices documented in .md files:
    - CAN FD: ATA6561 → ISOW1044BDFMR (5 kV reinforced isolation, integrated DC/DC)
    - RS-485: MAX3485E → ADM2795EBRWZ (5 kV reinforced isolation, ±42 V fault tolerance)
2026-06-04 Add EMI-hardened avionics variant schematics, PCBs, and transform scripts
    CAPE-A-2 (Flight Control & Sensor Cape — EMI-hardened):
    - SCH: ATA6561→ISOW1044BDFMR (5kV reinforced CAN isolation + DC/DC)
    - SCH: MAX3485E→ADM2795EBRWZ (5kV reinforced RS-485 isolation + DC/DC)
    - SCH: Both DP83825I PHYs removed; ADIN1300BCPZ + 2×ISO7642FDWRR ETH stack added
    - SCH: SRF2012-100Y CMCs on CAN/RS-485 field lines; PRTR5V0U2X TVS arrays
    - SCH: SMAJ33CA 1553 TVS; Würth 742792512 ferrite bead; X2Y bridging caps
2026-06-04 Add magnetometer, battery monitor, SBUS/XCVR mux to Cape-A/B; update v2 EMI variants
    Cape-A-1.kicad_sch (via add_sensors_sbus.py):
    - QMC5883L 3-axis magnetometer on I2C1 with GPIO_MAG_DRDY output
    - INA219AIDR battery voltage monitor on I2C1 (voltage-only, IN+/IN- tied)
    - J_VBAT JST GH 2P connector for VBAT_MON_P/GND
    - J_SBUS JST GH 3P → 100R R_SBUS → 74LVC1G14 Schmitt inverter → UART_SBUS_RX
    (SBUS is inverted UART 100kbaud 8E2; inverter restores standard logic)
2026-06-04 Add governor_config.h and governor_cal.py (TODO §4.2)
    Implements two open TODO items from section 4.2 of TODO.md:
    governor_config.h — compile-time EDF governor constants
    - Thrust model coefficients EDF_THRUST_K_* (T = k × RPM²) for all
    five EDF channels (PORT_FWD/AFT, STBD_FWD/AFT, FUSE), seeded with
    design estimates from manufacturer data sheets [1][2]. Inline
    CAL:<NAME> tags let governor_cal.py locate each constant for update.
2026-06-04 Add .gitignore for fc/tools Python bytecode cache
    Excludes __pycache__/, *.pyc, and *.pyo generated by governor_cal.py
    and any future host-side Python tools in this directory.
    https://claude.ai/code/session_019MRLDe1Fr9QW24ULRSoJgH
2026-06-04 Phase 6: add DTS overlays, serenity-common, and FC sensor drivers
    Device tree overlays (avionics/firmware/dts/):
    - cape-a v1: add I2C1 (QMC5883L@0x0D, INA219@0x40), UART2 SBUS pinmux
    - cape-a v2: new overlay for MMC5983MA@0x30, INA226@0x40, ADIN1300BCPZ
    - cape-b v1: update UART5 comment for DIP-switch XCVR/SBUS dual mode
    - cape-b v2: new overlay for ADIN1300BCPZ, EMI-hardened transceivers
    - Makefile: build and install all four overlays
2026-06-05 updated a lot of stuff
2026-06-05 updated the README and other documentation to reflect the current state of the project, including recent changes and updates to the archives and avionics sections. Also updated the LICENSE_AND_ATTRIB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
2026-06-05 updated px
2026-06-05 updated the xcvr to fix drc issues an
2026-06-05 report for xcrv-DRC.rpt
2026-06-05 Arch: document v2·v1·v1·v2 EMI-hardened node placement on internal data bus
    Establishes the architectural decision that EMI-hardened -2 capes are
    installed at both ends of the internal data bus (Bay A and Bay E) while
    standard -1 capes occupy the inner ring positions (Bay B and Bay D):
    Bay A (CN1/FC1): Cape-B-2 / Cape-A-2 — CAN FD/RS-485/1553B bus start
    termination; 5 kV isolated transceivers where external connectors and
    forward cable runs present the highest conducted-transient exposure.
2026-06-05 avionics/CAPE-B-2: add §13 antenna filter chains (EMI hardening)
    Each on-board RF transceiver now has a dedicated filtered antenna path:
    - FL_LORA / FL_SIK: Johanson 0915LP15B0100E BPF (902–928 MHz, 0.6 dB IL)
    - FL_WIFI: Johanson 2450BP15B050E BPF (2400–2500 MHz, 0.5 dB IL)
    - D_ANT_LORA / D_ANT_WIFI / D_ANT_SIK: Semtech RCLAMP0502BTCL ESD shunt
    (0.15 pF — chosen to avoid antenna detuning at 915 / 2400 MHz)
    - J_SMA_LORA / J_SMA_WIFI / J_SMA_SIK: SMA PCB bulkhead jacks, shells to PGND
2026-06-05 Revision Q: Hardened Avionics Baseline — EMI-hardened v2 capes at all positions; v1 and old design variants archived
    Rev Q is a comprehensive design checkpoint. Key changes:
    Avionics (v2-only standardisation):
    - All 8 nodes now use EMI-hardened v2 capes (Cape-A-2 / Cape-B-2 / XCVR-49MHZ-2)
    at every position. Placement: v2·v2·v2·v2 (was v2·v1·v1·v2). Inner bays B and D
    upgraded from v1 standard to v2 hardened capes.
    - Cape-A-1, Cape-B-1, XCVR-49MHZ-1 KiCad files archived to avionics/kicad/archive/
2026-06-06 Add shielded JST-GH connectors, wiring harness spec, Faraday enclosure, and bay fans
    Schematics (Cape-A-2, Cape-B-2, XCVR-49MHZ-2):
    - Added SHIELD/MP pin to all JST-GH connector symbol definitions, bonded to PGND
    - Added PGND power symbol definition to each schematic's lib_symbols
    - Added pin "MP" UUID to all connector instances (J_VBAT, J_SBUS, J_XCVR, J1)
    - Added PGND power symbol instance at each connector's MP mounting-tab pad
    - Added J_FAN 3-pin JST-GH connector to Cape-A-2 and Cape-B-2
2026-06-06 Add AS5600 hall-effect nacelle tilt encoder interface (Rev Q)
    - Cape-A-2: add Conn_JST_GH_04P and C_SMD symbol definitions to lib_symbols
    - Cape-A-2: add J_ENC 4-pin shielded JST-GH connector for I2C encoder bus
    (GND / +3V3 / ENC_SDA / ENC_SCL + PGND shield drain)
    - Cape-A-2: add 2.2 kΩ pull-up resistors R_ENC_SDA / R_ENC_SCL at host end
    - Cape-A-2: add 100 nF bypass cap C_ENC on +3V3 at J_ENC
    - Cape-A-2.md: add §13 documenting J_ENC pinout, I2C parameters, STP cable
2026-06-07 feat: complete battery and power distribution system (Rev Q)
    Hardware (PDB-2):
    - avionics/kicad/PDB-2.md: custom 4-layer 90×65 mm power distribution
    board spec replacing generic PDB-BEC; dual redundant 5 V/10 A SMPS
    (TPS54620 × 2, diode-OR'd); 6 V/5 A servo SMPS (TPS54540); 150 A
    MAXI main fuse + 4 × 40 A mini-blade ESC branch fuses; hardware-
    coordinated protection (40 A branch clears first on ESC short);
2026-06-07 feat(pdb2): per-EDF isolation, shield ground, harness spec, FC signal routing
    PDB-2.md:
    - ESC branch schematic: add three-layer stall isolation (Layer 2: C_DECn
    470 µF per-output bulk cap; Layer 3: CM_ESCn Würth 7440640500 per-output
    CM choke) with J_SHLD_ESCn chassis ground lugs for cable shield drain.
    - Connectors section: add J_PGND_BATT, J_SHLD_ESC1–5, J_SHLD_5V/6V, and
    PGND via-pads J_SHLD_I2C/ALERT/NTC so every connector has a shield ground
2026-06-07 Phase 11 Rev Q: EMI hardening, battery mount, Kaylee rename
    EMI hardening (500 W/m² design target):
    - Kaylee.md: two-stage CM filter (CM1+CM2 Würth 7440640500, ~80 dB cascade),
    Y-caps C_Y1/C_Y2 (4.7 nF/250 V Y2, Kemet SA305E472MAR) to chassis,
    DM bypass C_DM1 (10 µF X7R 1210), I2C TVS D_I2C (NXP PRTR5V0U2X),
    shielded 1.5 mm 6061-T6 aluminum enclosure + CHO-SEAL 1217 gasket (≥60 dB SE),
    Pflitsch 750M-series EMC cable glands (360° shield bond), J_CHASSIS pad.
2026-06-07 Add PWR-DIST-1 power distribution board and VTOL thrust analysis (Rev Q)
    - docs/POWER_SYSTEM_Q.md: complete power system analysis for Rev Q.
    Documents the critical VTOL thrust deficit: 50mm budget EDFs produce
    T/W = 0.48:1 (cannot hover). Phase 7 XRP 80mm EDFs reach T/W = 1.34:1
    (marginal). Corrects the erroneous T/W = 1.47 figure in README that
    incorrectly summed the horizontal rear EDF into vertical VTOL lift.
    Includes battery sizing, wire gauge table, ESC selection, MIL-B-5087B
2026-06-07 Rev Q: Wash/Zoë Ethernet PHYs, field connectors, Rev Q documentation propagation
    Implements TODO tasks 1.4.2–1.4.5 and 1.5.1. Renames Cape-B-2 callsign
    from "Mr. Universe" to "Zoë" throughout per CLAUDE.md (2026-06-07).
    Wash (CAPE-A-2) — task 1.4.2 + 1.4.4:
    - Dual EMI-hardened Ethernet PHY: DP83825I ×2 (RMII0→PHY1 addr 0x01,
    RMII1→PHY2 addr 0x02); HX1188NL magnetics ×2; TPS62933 1.8V ×2;
    PRTR5V0U2X TVS ×4; SRF2012-100Y CMC ×2; J_ETH1 + J_ETH2 (SM06B-GHS)
2026-06-08 updated stuff
2026-06-08 update todo
2026-06-08 added more stuff
2026-06-08 fixed stuff
2026-06-09 docs(power): archive POWER_SYSTEM_Q + PWR-DIST-1; add §§12-14 to POWER_DISTRIBUTION
    Archive superseded documents:
    - docs/POWER_SYSTEM_Q.md → archives/docs-superseded/ (phase numbering mismatch,
    wrong EDF spec 228g vs XFly 1240g, wrong AUW, wrong connector/fuse sizing)
    - avionics/kicad/PWR-DIST-1.kicad_sch → avionics/kicad/archive/ (old design:
    ANL fuse, ACS758, AS150 connector, UBEC modules — superseded by Kaylee design)
    - avionics/kicad/PWR-DIST-1.md → avionics/kicad/archive/
2026-06-09 fixed the stuffs
2026-06-10 feat(avionics): generate Kaylee PDB KiCad files (pro/sch/pcb) Rev A
    - Kaylee.kicad_pro: project settings, 4 net classes (VBAT 6mm trace,
    PGND 6mm, POWER_5V 0.5mm, Default 0.3mm), DRC rules (0.15mm clearance)
    - Kaylee.kicad_sch: complete 229 kB schematic on A1 sheet, all sections:
    battery input (CM1+CM2 two-stage EMI filter), main bus disconnect FET
    (AON6556 + BQ76930 DSG gate), main INA226 shunt (0x44), 4× ESC branches
    (fuse/decap/CMC/shunt/INA226 per branch, 0x40-0x43), ESC5 DNP (Phase 11),
2026-06-10 added the Capt'n
2026-06-11 chore(revision): propagate Rev R designation to all active files
    - Update all project-level revision headers from Rev Q → Rev R (2026-06-11)
    - Add Rev R changelog entry to all five fuselage SCAD files
    (s_head_shell24, s_middle_canonical_shell24, s_rear_shell24,
    battery_tray, belly_panel)
    - Update GCS Malcolm files from R1 (Q1 → R1, 2026-06-10 → 2026-06-11)
    across firmware headers, SCAD, Python tracking stack, and docs
2026-06-11 chore(revision): synchronise avionics component designations to Rev R
    Per CLAUDE.md: all components referenced as of the latest project revision.
    Wash.md — Rev A → Rev R; date 2026-06-02 → 2026-06-11;
    section "new in Rev A" → "Rev R baseline; introduced Rev A"
    Kaylee.md — title + Revision field Rev A → Rev R; date → 2026-06-11
    XCVR-49MHZ-2.md — Rev A → Rev R; date 2026-06-02 → 2026-06-11
    Zoë.md — section "Rev A addition" → "Rev R baseline; introduced Rev A"
2026-06-12 fix: correct Cape-A/B PCB dimensions to 55×35 mm in BOMs and Zoë docs
    Wash (Cape-A-2) and Zoë (Cape-B-2) PCBs are 55×35 mm per Edge.Cuts in
    Wash.kicad_pcb and Zoë.kicad_pcb. All active documents updated:
    - current-specification/bom_revR.csv: CAPE-A, CAPE-A-2, CAPE-B, CAPE-B-2
    and MAL-ENCLOSURE entries corrected (85x55→55x35, 90x60→55x35)
    - current-specification/bom_revQ.csv: same corrections
    - avionics/kicad/Zoë.md: CAPE-B-1 footprint reference corrected to 55×35 mm
2026-06-12 fix: correct all remaining cape PCB dimension references to 55×35 mm
    Wash (Cape-A-2) and Zoë (Cape-B-2) — and the Cape-A-1/Cape-B-1 predecessors
    they replaced — are all 55×35 mm PCBs per Edge.Cuts. Corrects the incorrect
    early estimates (85×55 and 90×60) that propagated into documentation.
    Files updated:
    - TODO.md: panel-cut sizes (85×55→62×42, 90×60→55×35), bay footprint references,
    Simon stack note, Malcolm enclosure note; standoff hole patterns flagged TBD
2026-06-12 fixed some stuff
2026-06-14 Add standards vetting policy, REFERENCES.md catalog, and propagate REF-IDs throughout codebase
    Creates REFERENCES.md: authoritative catalog of all applicable standards and regulations,
    each with a validated official URL, specific chapter/section/paragraph applied, and every
    repo location where the standard is cited. Adds Standards Vetting Policy to CLAUDE.md
    requiring that all non-cosmetic design decisions cite verifiable standards by REF-ID with
    chapter/section/paragraph.
    Fixes incorrect citation: removes "NIST SP 800-72 write-blocker principles" from README.md
2026-06-15 ignoring kicad history
2026-06-16 fixed
2026-06-19 updated zoe and emma boards. renamed all xcvr files to emma. updated project index to reflect the name change.
2026-06-19 updated avionics and docs
2026-06-22 added the stuff
2026-06-29 updated standards stuff

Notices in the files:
kicad/Kaylee/kicads/Kaylee.kicad_pcb:
CC BY 4.0 creativecommons.org/licenses/by/4.0
Griffing Technology LLC | CC BY 4.0
kicad/Kaylee/scripts/gen_kaylee.py:
CC BY 4.0" (at {W/2:.2f} {H + 5.0:.2f} 0)'
kicad/Zoë/kicads/Zoë.kicad_pcb:
Hull: misubisu CC BY 4.0 | Nozzle: BamJr CC BY 4.0 | Firefly/Serenity fan-work, not officially licensed
CC BY 4.0 — May 2026
